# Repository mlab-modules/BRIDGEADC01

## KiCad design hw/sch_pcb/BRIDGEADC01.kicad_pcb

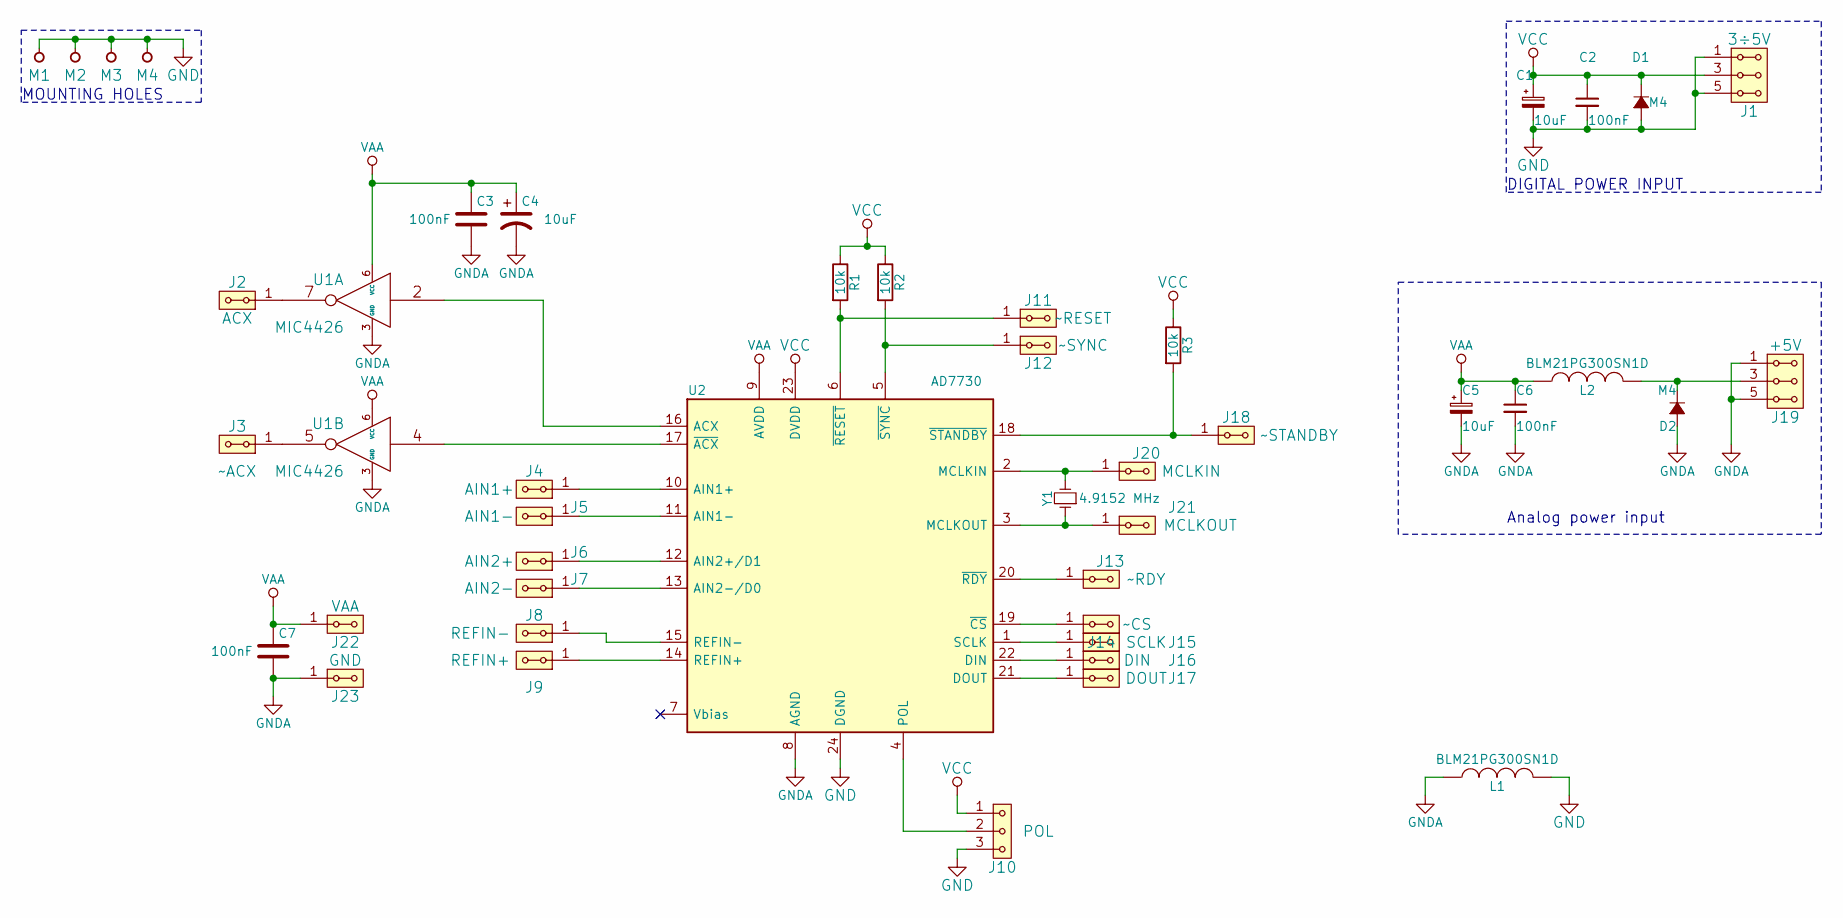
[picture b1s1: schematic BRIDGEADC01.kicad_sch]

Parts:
C1, C4, C5: 10uF; TantalC_SizeB_EIA-3528_Reflow
C2, C3, C6, C7: 100nF; C_0805
D1, D2: M4; SMA_Standard
J1: 3÷5V; Straight_2x03
J2: ACX; Straight_1x02
J3: ~ACX; Straight_1x02
J4: AIN1+; Straight_1x02
J5: AIN1-; Straight_1x02
J6: AIN2+; Straight_1x02
J7: AIN2-; Straight_1x02
J8: REFIN-; Straight_1x02
J9: REFIN+; Straight_1x02
J10: POL; Straight_1x03
J11: ~RESET; Straight_1x02
J12: ~SYNC; Straight_1x02
J13: ~RDY; Straight_1x02
J14: ~CS; Straight_1x02
J15: SCLK; Straight_1x02
J16: DIN; Straight_1x02
J17: DOUT; Straight_1x02
J18: ~STANDBY; Straight_1x02
J19: +5V; Straight_2x03
J20: MCLKIN; Straight_1x02
J21: MCLKOUT; Straight_1x02
J22: VAA; Straight_1x02
J23: GND; Straight_1x02
L1, L2: BLM21PG300SN1D; C_0805
M1, M2, M3, M4: HOLE; MountingHole_3mm
R1, R2, R3: 10k; R_0805
U1: MIC4426; SOIC-8_3.9x4.9mm_Pitch1.27mm
U2: AD7730; TSSOP-24_4.4x7.8mm_Pitch0.65mm
Y1: 4.9152 MHz; Crystal_HC49-U_Vertical

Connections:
GND: C1.2, C2.2, D1.2 (A), J1.1, J1.2, J1.5, J1.6, J10.3, L1.2, M1.1, M2.1, M3.1, M4.1, U2.24 (DGND)
GNDA: C3.2, C4.2, C5.2, C6.2, C7.2, D2.2 (A), J19.1, J19.2, J19.5, J19.6, J23.1, J23.2, L1.1, U1.3 (GND), U2.8 (AGND)
unnamed: D2.1 (K), J19.3, J19.4, L2.2
unnamed: J2.1, J2.2, U1.7
unnamed: J3.1, J3.2, U1.5
unnamed: J4.1, J4.2, U2.10 (AIN1+)
unnamed: J5.1, J5.2, U2.11 (AIN1-)
unnamed: J6.1, J6.2, U2.12 (AIN2+/D1)
unnamed: J7.1, J7.2, U2.13 (AIN2-/D0)
unnamed: J8.1, J8.2, U2.15 (REFIN-)
unnamed: J9.1, J9.2, U2.14 (REFIN+)
unnamed: J10.2, U2.4 (POL)
unnamed: J11.1, J11.2, R1.2, U2.6 (~RESET)
unnamed: J12.1, J12.2, R2.2, U2.5 (~SYNC)
unnamed: J13.1, J13.2, U2.20 (~RDY)
unnamed: J14.1, J14.2, U2.19 (~CS)
unnamed: J15.1, J15.2, U2.1 (SCLK)
unnamed: J16.1, J16.2, U2.22 (DIN)
unnamed: J17.1, J17.2, U2.21 (DOUT)
unnamed: J18.1, J18.2, R3.2, U2.18 (~STANDBY)
unnamed: J20.1, J20.2, U2.2 (MCLKIN), Y1.2
unnamed: J21.1, J21.2, U2.3 (MCLKOUT), Y1.1
unnamed: U1.2, U2.16 (ACX)
unnamed: U1.4, U2.17 (~ACX)
VAA: C3.1, C4.1, C5.1, C6.1, C7.1, J22.1, J22.2, L2.1, U1.6 (VCC), U2.9 (AVDD)
VCC: C1.1, C2.1, D1.1 (K), J1.3, J1.4, J10.1, R1.1, R2.1, R3.1, U2.23 (DVDD)

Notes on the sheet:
Analog power input
DIGITAL POWER INPUT
MOUNTING HOLES

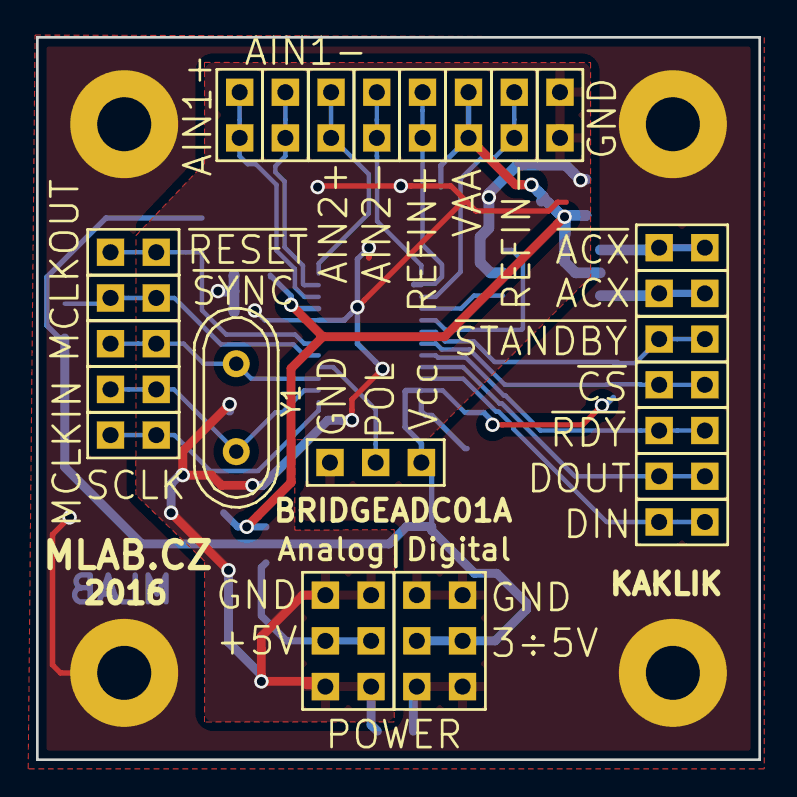
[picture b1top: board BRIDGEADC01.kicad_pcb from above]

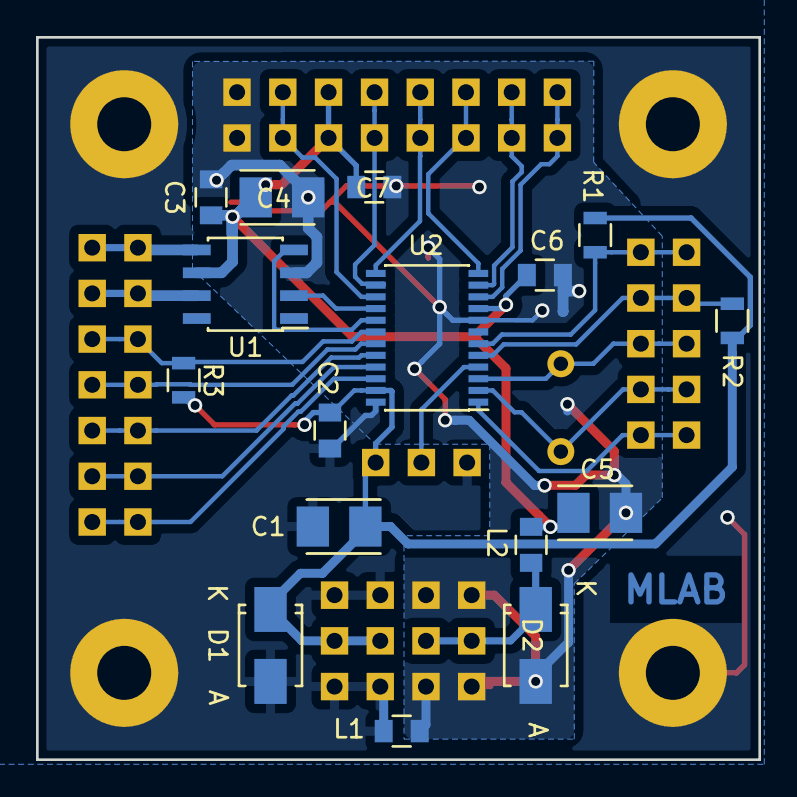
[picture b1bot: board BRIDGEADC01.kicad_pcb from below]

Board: 2 copper layers, 40.1 x 40.1 mm, 44 parts (16 on the bottom side), 26 nets.

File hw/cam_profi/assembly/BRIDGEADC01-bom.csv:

Component,Description,Part,References,Value,Footprint,Quantity Per PCB,Datasheet,ust_id
1,,C_Small,C2C3C6C7,100nF,C_0805,4,,5c70984712875079b91f8b4c
2,,CP_Small,C1C5,10uF,TantalC_SizeB_EIA-3528_Reflow,2,,5c70984412875079b91f8865
3,,CP1,C4,10uF,TantalC_SizeB_EIA-3528_Reflow,1,,5c70984412875079b91f8865
4,,D_Small,D1D2,M4,SMA_Standard,2,,5c70984512875079b91f88ac
5,,HEADER_2x03_PARALLEL,J19,+5V,Straight_2x03,1,,
6,,HEADER_2x03_PARALLEL,J1,3÷5V,Straight_2x03,1,,
7,,HEADER_2x01_PARALLEL,J2,ACX,Straight_1x02,1,,
8,,HEADER_2x01_PARALLEL,J4,AIN1+,Straight_1x02,1,,
9,,HEADER_2x01_PARALLEL,J5,AIN1-,Straight_1x02,1,,
10,,HEADER_2x01_PARALLEL,J6,AIN2+,Straight_1x02,1,,
11,,HEADER_2x01_PARALLEL,J7,AIN2-,Straight_1x02,1,,
12,,HEADER_2x01_PARALLEL,J16,DIN,Straight_1x02,1,,
13,,HEADER_2x01_PARALLEL,J17,DOUT,Straight_1x02,1,,
14,,HEADER_2x01_PARALLEL,J23,GND,Straight_1x02,1,,
15,,HEADER_2x01_PARALLEL,J20,MCLKIN,Straight_1x02,1,,
16,,HEADER_2x01_PARALLEL,J21,MCLKOUT,Straight_1x02,1,,
17,,HEADER_1x03,J10,POL,Straight_1x03,1,,
18,,HEADER_2x01_PARALLEL,J9,REFIN+,Straight_1x02,1,,
19,,HEADER_2x01_PARALLEL,J8,REFIN-,Straight_1x02,1,,
20,,HEADER_2x01_PARALLEL,J15,SCLK,Straight_1x02,1,,
21,,HEADER_2x01_PARALLEL,J22,VAA,Straight_1x02,1,,
22,,HEADER_2x01_PARALLEL,J3,~ACX,Straight_1x02,1,,
23,,HEADER_2x01_PARALLEL,J14,~CS,Straight_1x02,1,,
24,,HEADER_2x01_PARALLEL,J13,~RDY,Straight_1x02,1,,
25,,HEADER_2x01_PARALLEL,J11,~RESET,Straight_1x02,1,,
26,,HEADER_2x01_PARALLEL,J18,~STANDBY,Straight_1x02,1,,
27,,HEADER_2x01_PARALLEL,J12,~SYNC,Straight_1x02,1,,
28,,INDUCTOR,L1L2,BLM21PG300SN1D,C_0805,2,,5c70984412875079b91f87fd
29,,R,R1R2R3,10k,R_0805,3,,5c70984612875079b91f899f
30,,AD7730,U2,AD7730,TSSOP-24_4.4x7.8mm_Pitch0.65mm,1,,5c70984612875079b91f8a14
31,,MIC4426,U1,MIC4426,SOIC-8_3.9x4.9mm_Pitch1.27mm,1,,5c70984612875079b91f8a06
32,,Crystal_Small,Y1,4.9152 MHz,Crystal_HC49-U_Vertical,1,,5c70984712875079b91f8b0d

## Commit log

2017-08-24 Renaming top directories.
2018-02-26 Oprava spatnych cest po prenosu dokumentu
2018-04-11 [MLABweb] Documentaion edits; BRIDGEADC01A
2018-11-05 Presun obrazku do slozky img. Pregenerovani dokumentaci.
2019-04-25 [MLABweb] Documentation edits; BRIDGEADC01A
2019-08-17 Improve project descriptions for ADC modules
2020-11-04 Fix license
2021-05-18 Edit production data
2021-06-08 Edit
2021-06-16 Edit UST_ID
2021-08-05 Move to issue #1
2022-04-06 automated commit; add github actions
2022-04-06 Update actions products
2023-05-25 Update metadata files
2023-05-28 Update workflow files
2023-07-05 automated commit; rename source files to new naming convence
2023-07-05 aktualizace repozitare
2023-09-15 Update metadata.yaml
    Change the title image.
2023-09-15 Update metadata.yaml
    change title image.
